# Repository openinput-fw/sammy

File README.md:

# sammy

Open source wired mouse hardware.

The little brother of [big-sammy](https://github.com/openinput-fw/big-sammy).

Please see the [documentation](https://sammy.readthedocs.io/en/latest)
for more information.

## Specifications
- 8 kHz sampling rate support
- Zero latency switch debounce
- Onboard configuration memory
- 2 main mouse buttons (satellite* configuration for both)
- 2 side buttons (symmetric to allow easy left/right handedness)
- encoder + wheel button (satellite* configuration)
- RGB Led

`*meaning, a separate board from the core with the controller and sensor`

## Firmware

*sammy* is meant to run on [openinput](https://github.com/openinput-fw/openinput).

## License

This hardware is licensed under the [CERN-OHL-P v2](LICENSE) license.

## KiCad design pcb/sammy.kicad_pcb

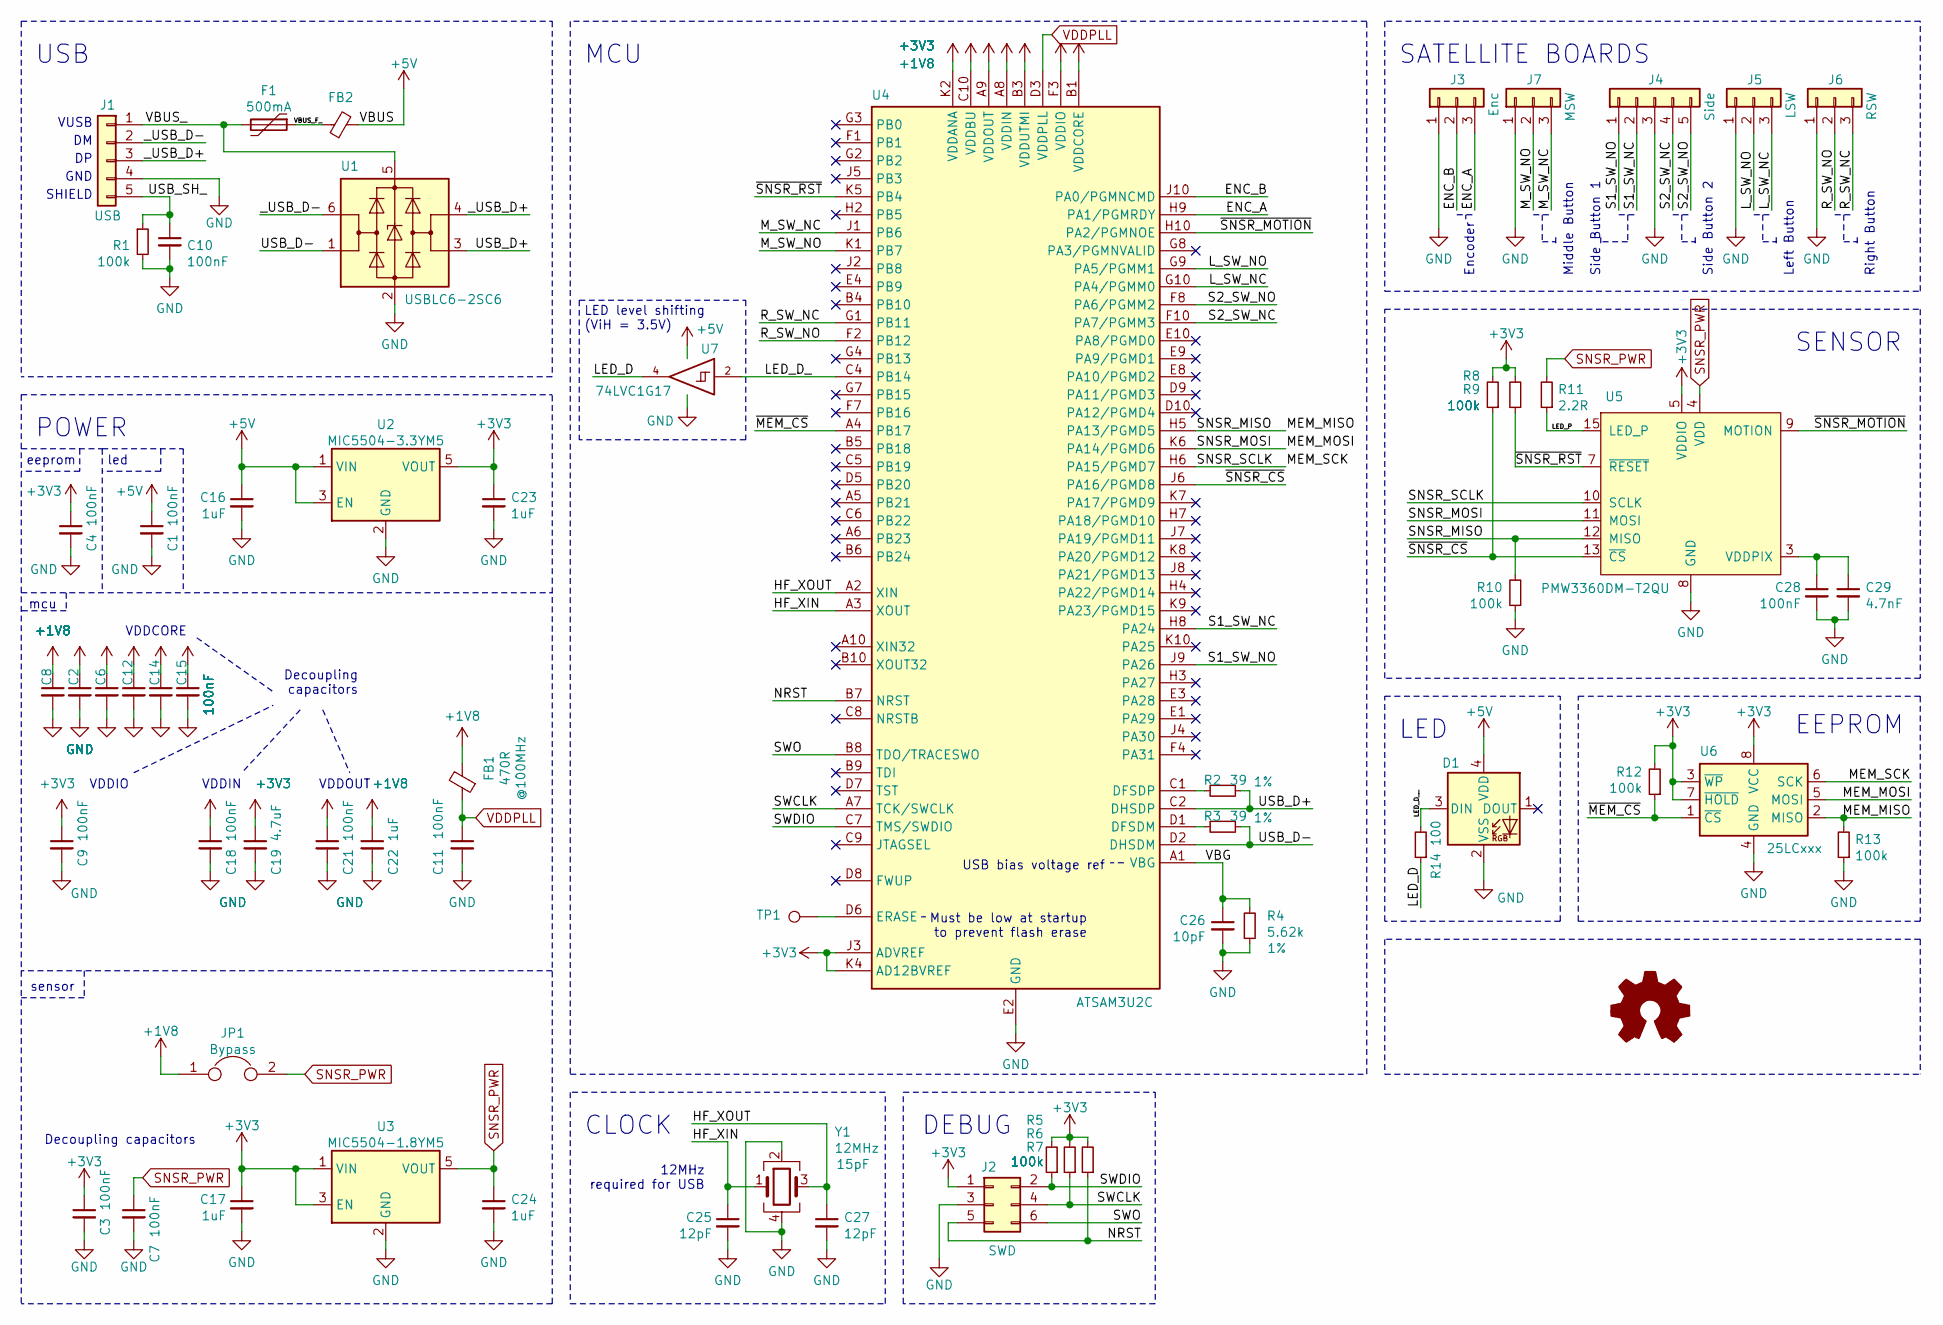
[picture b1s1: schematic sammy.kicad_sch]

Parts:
C1, C2, C3, C4, C6, C7, C8, C9, C10, C11, C12, C14, C15, C18, C21, C28: 100nF; C_0402_1005Metric
C16, C17, C22, C23, C24: 1uF; C_0603_1608Metric
C19: 4.7uF; C_0603_1608Metric
C25, C27: 12pF; C_0402_1005Metric
C26: 10pF; C_0402_1005Metric
C29: 4.7nF; C_0402_1005Metric
D1: ws2812-2020
F1: 500mA; Fuse_0603_1608Metric_Castellated
FB1: 470R; L_0402_1005Metric
FB2: L_0402_1005Metric
J1: USB; JST_PH_B5B-PH-K_1x05_P2.00mm_Vertical
J2: SWD; Tag-Connect_TC2030-IDC-NL_2x03_P1.27mm_Vertical
J3: Enc; JST_SH_BM03B-SRSS-TB_1x03-1MP_P1.00mm_Vertical
J4: Side; JST_SH_BM05B-SRSS-TB_1x05-1MP_P1.00mm_Vertical
J5: LSW; JST_SH_BM03B-SRSS-TB_1x03-1MP_P1.00mm_Vertical
J6: RSW; JST_SH_BM03B-SRSS-TB_1x03-1MP_P1.00mm_Vertical
J7: MSW; JST_SH_BM03B-SRSS-TB_1x03-1MP_P1.00mm_Vertical
JP1: Bypass; SolderJumper-2_P1.3mm_Open_RoundedPad1.0x1.5mm
R1, R5, R6, R7, R8, R9, R10, R12, R13: 100k; R_0402_1005Metric
R2, R3: 39; R_0402_1005Metric; Tolerance 1%
R4: 5.62k; R_0402_1005Metric; Tolerance 1%
R11: 2.2R; R_0402_1005Metric
R14: 100; R_0402_1005Metric
TP1: TestPoint_Pad_D1.0mm
U1: USBLC6-2SC6; SOT-23-6
U2: MIC5504-3.3YM5; SOT-23-5
U3: MIC5504-1.8YM5; SOT-23-5
U4: ATSAM3U2C; TFBGA-100_9.0x9.0mm_Layout10x10_P0.8mm
U5: PMW3360DM-T2QU; PMW3360
U6: 25LCxxx; DFN-S-8-1EP_6x5mm_P1.27mm
U7: 74LVC1G17; SOT-353_SC-70-5
Y1: 12MHz; Crystal_SMD_3225-4Pin_3.2x2.5mm

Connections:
+1V8: C2.1, C6.1, C8.1, C12.1, C14.1, C15.1, C21.1, C22.1, FB1.2, JP1.1, U4.A9 (VDDOUT), U4.B1 (VDDCORE), U4.D4 (VDDCORE), U4.E7 (VDDCORE), U4.F9 (VDDCORE), U4.G5 (VDDCORE), U4.H1 (VDDCORE)
+3V3: C3.1, C4.1, C9.1, C17.1, C18.1, C19.1, C23.1, J2.1, R5.2, R6.2, R7.2, R8.2, R9.2, R12.2, U2.5 (VOUT), U3.1 (VIN), U3.3 (EN), U4.A8 (VDDIN), U4.B3 (VDDUTMI), U4.C10 (VDDBU), U4.E6 (VDDIO), U4.F3 (VDDIO), U4.F5 (VDDIO), U4.J3 (ADVREF), U4.K2 (VDDANA), U4.K4 (AD12BVREF), U5.5 (VDDIO), U6.3 (~WP), U6.7 (~HOLD), U6.8 (VCC)
+5V: C1.1, C16.1, D1.4 (VDD), FB2.2, U2.1 (VIN), U2.3 (EN), U7.5 (VCC)
/ENC_A: J3.3, U4.H9 (PA1/PGMRDY)
/ENC_B: J3.2, U4.J10 (PA0/PGMNCMD)
/HF_XIN: C25.1, U4.A3 (XOUT), Y1.1
/HF_XOUT: C27.1, U4.A2 (XIN), Y1.3
/LED_D: R14.1, U7.4
/LED_D_: U4.C4 (PB14), U7.2
/LED_D__: D1.3 (DIN), R14.2
/LED_P: R11.1, U5.15 (LED_P)
/L_SW_NC: J5.3, U4.G10 (PA4/PGMM0)
/L_SW_NO: J5.2, U4.G9 (PA5/PGMM1)
/MEM_MISO: R10.2, R13.2, U4.H5 (PA13/PGMD5), U5.12 (MISO), U6.2 (MISO)
/MEM_MOSI: U4.K6 (PA14/PGMD6), U5.11 (MOSI), U6.5 (MOSI)
/MEM_SCK: U4.H6 (PA15/PGMD7), U5.10 (SCLK), U6.6 (SCK)
/M_SW_NC: J7.3, U4.J1 (PB6)
/M_SW_NO: J7.2, U4.K1 (PB7)
/NRST: J2.5, R7.1, U4.B7 (NRST)
/R_SW_NC: J6.3, U4.G1 (PB11)
/R_SW_NO: J6.2, U4.F2 (PB12)
/S1_SW_NC: J4.2, U4.H8 (PA24)
/S1_SW_NO: J4.1, U4.J9 (PA26)
/S2_SW_NC: J4.4, U4.F10 (PA7/PGMM3)
/S2_SW_NO: J4.5, U4.F8 (PA6/PGMM2)
/SWCLK: J2.4, R6.1, U4.A7 (TCK/SWCLK)
/SWDIO: J2.2, R5.1, U4.C7 (TMS/SWDIO)
/SWO: J2.6, U4.B8 (TDO/TRACESWO)
/USB_D+: R2.1, U1.3 (I/O2), U4.C2 (DHSDP)
/USB_D-: R3.1, U1.1 (I/O1), U4.D2 (DHSDM)
/USB_SH_: C10.1, J1.5, R1.1
/VBG: C26.1, R4.2, U4.A1 (VBG)
/VBUS_: F1.2, J1.1, U1.5 (VBUS)
/VBUS_F_: F1.1, FB2.1
/_USB_D+: J1.3, U1.4 (I/O2)
/_USB_D-: J1.2, U1.6 (I/O1)
/~MEM_CS: R12.1, U4.A4 (PB17), U6.1 (~CS)
/~SNSR_CS: R8.1, U4.J6 (PA16/PGMD8), U5.13 (~CS)
/~SNSR_MOTION: U4.H10 (PA2/PGMNOE), U5.9 (MOTION)
/~SNSR_RST: R9.1, U4.K5 (PB4), U5.7 (~RESET)
GND: C1.2, C2.2, C3.2, C4.2, C6.2, C7.2, C8.2, C9.2, C10.2, C11.2, C12.2, C14.2, C15.2, C16.2, C17.2, C18.2, C19.2, C21.2, C22.2, C23.2, C24.2, C25.2, C26.2, C27.2, C28.2, C29.2, D1.2 (VSS), J1.4, J2.3, J3.1, J4.3, J5.1, J6.1, J7.1, R1.2, R4.1, R10.1, R13.1, U1.2 (GND), U2.2 (GND), U3.2 (GND), U4.B2 (GNDUTMI), U4.C3 (GNDPLL), U4.E2 (GND), U4.E5 (GNDBU), U4.F6 (GND), U4.G6 (GND), U4.K3 (GNDANA), U5.8 (GND), U6.4 (GND), U7.3 (GND), Y1.2, Y1.4
unnamed: C28.1, C29.1, U5.3 (VDDPIX)
unnamed: TP1.1, U4.D6 (ERASE)
unnamed: R2.2, U4.C1 (DFSDP)
unnamed: R3.2, U4.D1 (DFSDM)
SNSR_PWR: C7.1, C24.1, JP1.2, R11.2, U3.5 (VOUT), U5.4 (VDD)
VDDPLL: C11.1, FB1.1, U4.D3 (VDDPLL)

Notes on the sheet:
Side Button 2
Left Button
DEBUG
USB
CLOCK
SENSOR
USB bias voltage ref
VDDCORE
SHIELD
Right Button
VUSB
led
MCU
12MHz required for USB
mcu
Decoupling capacitors
Side Button 1
GND
POWER
sensor
Encoder
Middle Button
eeprom
SATELLITE BOARDS
Decoupling capacitors
VDDIO
LED
LED level shifting (ViH = 3.5V)
VDDIN
Must be low at startup to prevent flash erase
EEPROM
VDDOUT

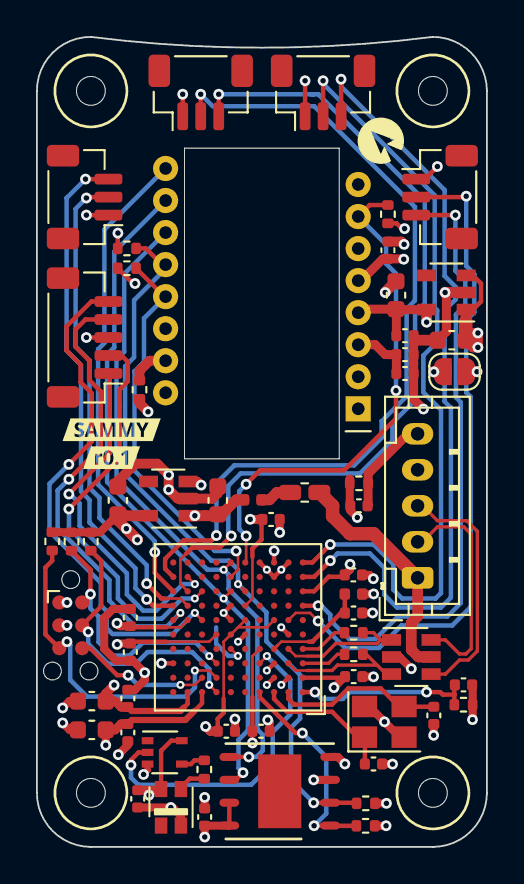
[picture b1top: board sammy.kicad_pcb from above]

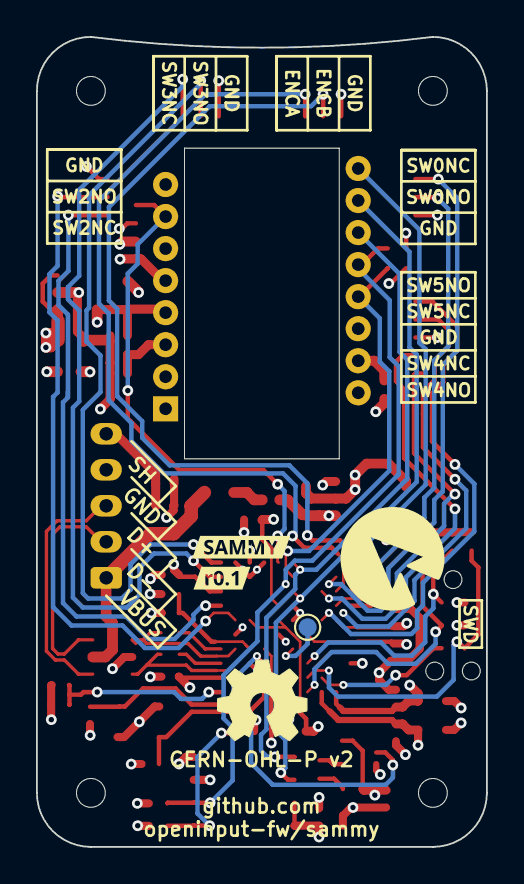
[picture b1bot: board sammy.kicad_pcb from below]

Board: 4 copper layers, 25.0 x 45.0 mm, 65 parts (3 on the bottom side), 47 nets.

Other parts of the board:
svg2mod, svg2mod#2, svg2mod#3, svg2mod#4: G***; svg2mod

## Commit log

2021-04-27 license: add CERN-OHL-P v2 license
2021-04-27 assets: add logo
2021-04-27 kicad: add local libraries (copy from big-sammy + atsam3u)
2021-04-27 git: add gitignore
2021-04-27 pcb: r0.1 schematic and layout based on big-sammy
2021-04-27 assets: add r0.1 render
2021-04-27 readme: add readme
2021-04-27 pcb: document label creation
2021-04-27 pcb: change minimum via diameter to 0.45mm
2021-04-30 pcb: move kicad project
2021-04-30 kicad: removed unused libs
2021-06-07 fix #2: typo in link to source
2021-06-07 fix #1: Connection to the usb peripheral is not correct
2021-07-02 readme: add peripheral board reference
2021-11-22 assets: move assets to docs
2021-11-22 docs: add readthedocs documentation
2021-11-23 readme: link to documentation
2021-11-23 docs: fix big-sammy link
2021-12-15 readme: formating
2021-12-15 readme: formatting
2022-01-07 kicad: save pcb with v6.0

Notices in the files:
pcb/sammy.kicad_pcb:
This source describes Open Hardware and is licensed under the CERN-OHL-Pv2
Copyright (c) Rafael Silva
